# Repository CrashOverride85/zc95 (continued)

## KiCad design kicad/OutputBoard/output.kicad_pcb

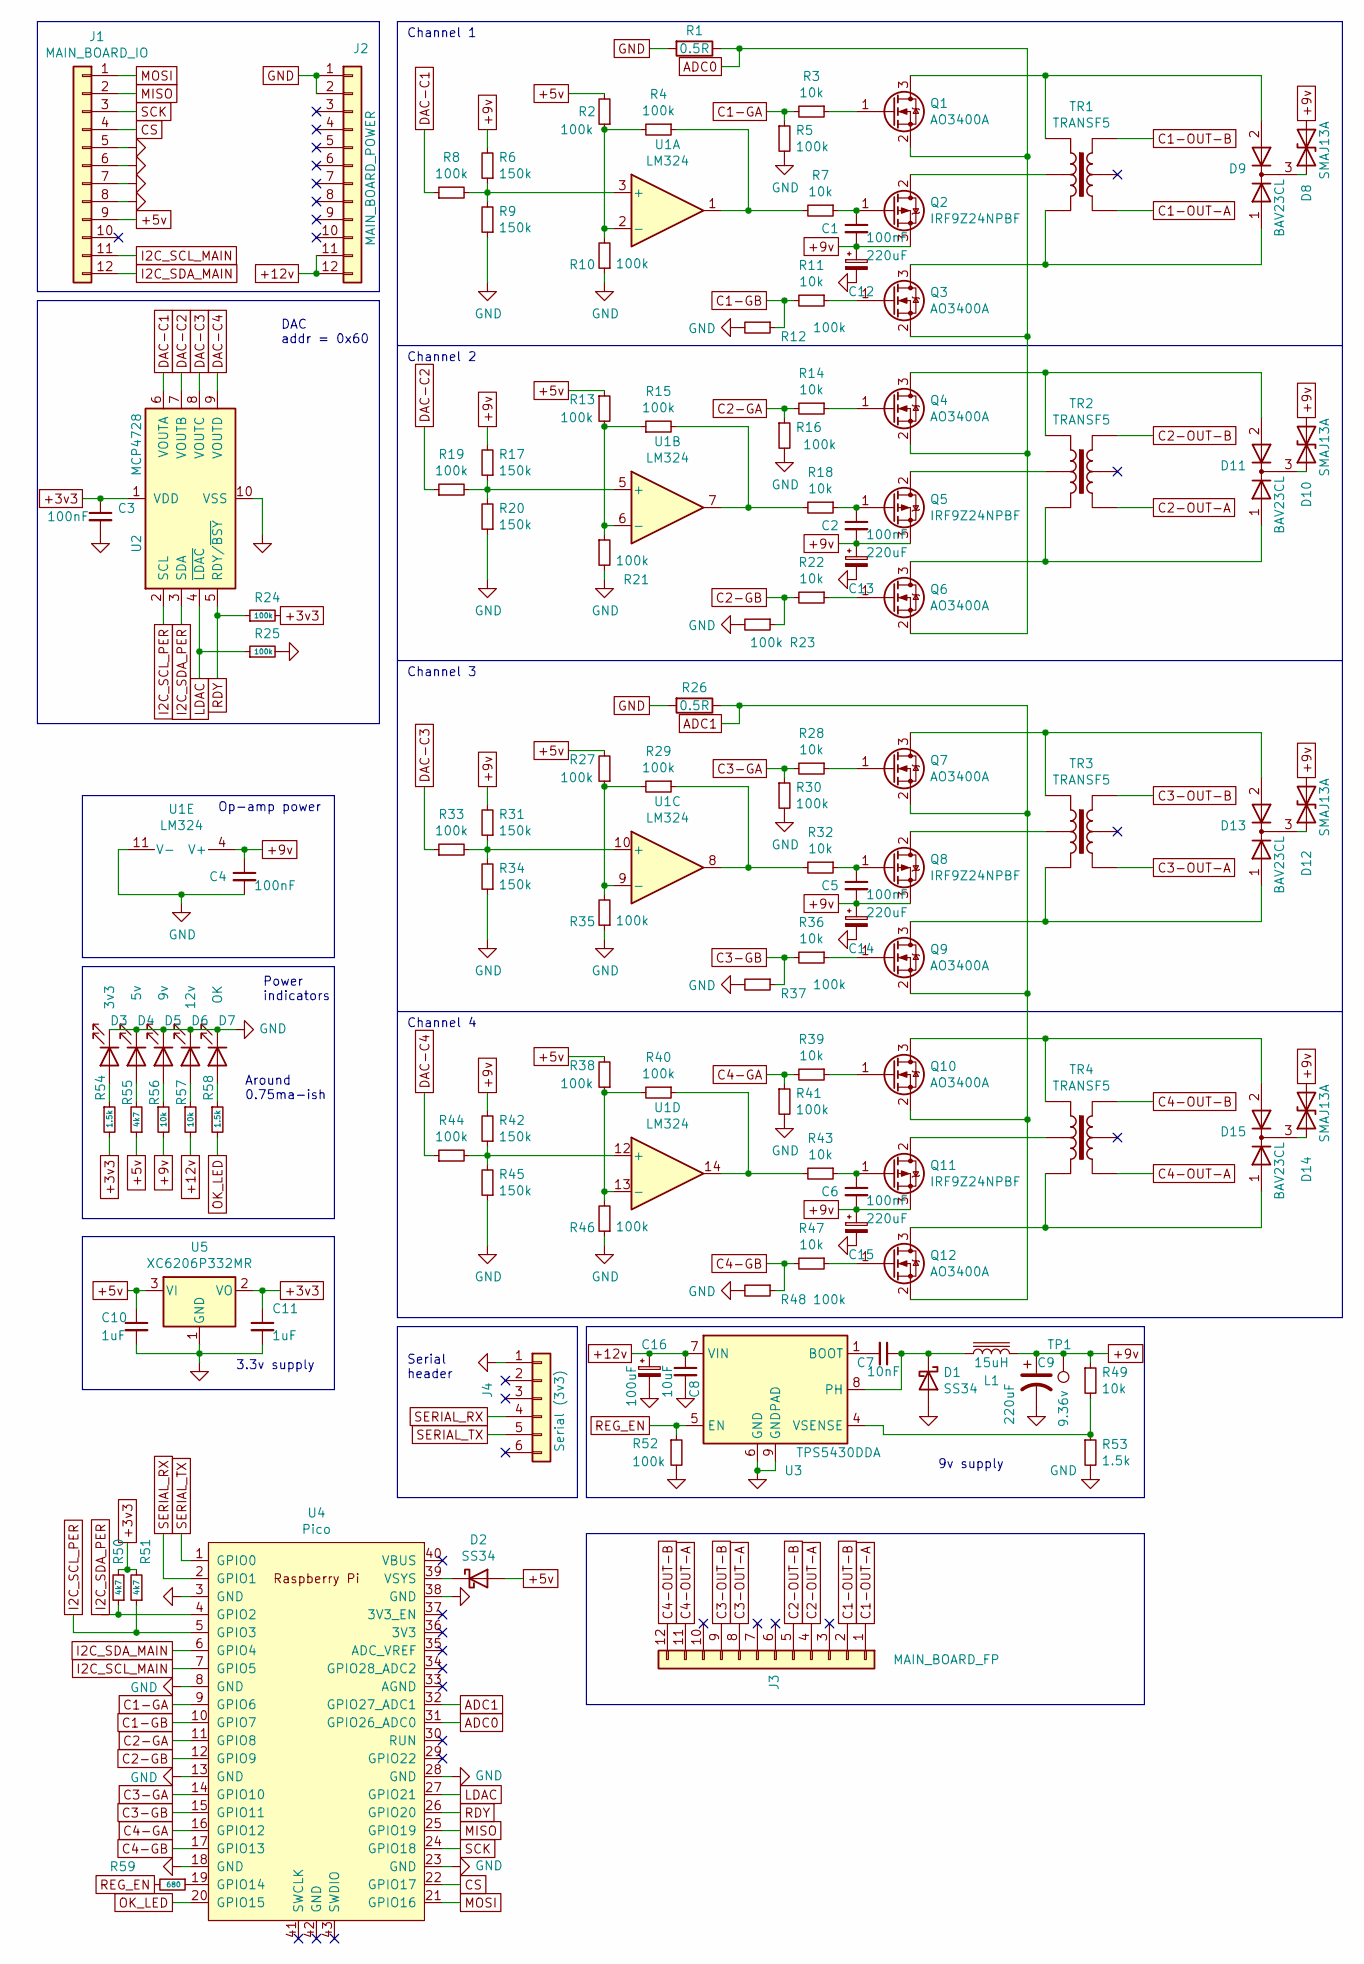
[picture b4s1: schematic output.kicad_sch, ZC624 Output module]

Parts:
C1, C2, C3, C4, C5, C6: 100nF; C_0603_1608Metric_Pad1.08x0.95mm_HandSolder; LCSC C49678
C7: 10nF; C_0603_1608Metric_Pad1.08x0.95mm_HandSolder; LCSC C57112
C8: 10uF; C_0603_1608Metric_Pad1.08x0.95mm_HandSolder; LCSC C15850
C9: 220uF; CP_Radial_D8.0mm_P3.50mm; LCSC C440836
C10, C11: 1uF; C_0603_1608Metric_Pad1.08x0.95mm_HandSolder; LCSC C28323
C12, C13, C14, C15: 220uF; CP_EIA-7343-43_Kemet-X_Pad2.25x2.55mm_HandSolder; LCSC C122311
C16: 100uF; CP_Radial_D5.0mm_P2.00mm; LCSC C108360
D1, D2: SS34; D_SMA; LCSC C8678
D3: 3v3; LED_0603_1608Metric_Pad1.05x0.95mm_HandSolder; LCSC C2986059
D4: 5v; LED_0603_1608Metric_Pad1.05x0.95mm_HandSolder; LCSC C2986059
D5: 9v; LED_0603_1608Metric_Pad1.05x0.95mm_HandSolder; LCSC C2986059
D6: 12v; LED_0603_1608Metric_Pad1.05x0.95mm_HandSolder; LCSC C2986059
D7: OK; LED_0603_1608Metric_Pad1.05x0.95mm_HandSolder; LCSC C2986059
D8, D10, D12, D14: SMAJ13A; D_SMA; LCSC C110519
D9, D11, D13, D15: BAV23CL; SOT-23-3; LCSC C232533
J1: MAIN_BOARD_IO; PinHeader_1x12_P2.54mm_Vertical
J2: MAIN_BOARD_POWER; PinHeader_1x12_P2.54mm_Vertical
J3: MAIN_BOARD_FP; PinHeader_1x12_P2.54mm_Vertical
J4: Serial (3v3); PinHeader_1x06_P2.54mm_Vertical
L1: 15uH; L_7.3x7.3_H3.5; LCSC C177243
Q1, Q3, Q4, Q6, Q7, Q9, Q10, Q12: AO3400A; SOT-23_Handsoldering; LCSC C20917
Q2, Q5, Q8, Q11: IRF9Z24NPBF; TO-220-3_Vertical; LCSC C2576
R1, R26: 0.5R; R_Axial_DIN0309_L9.0mm_D3.2mm_P5.08mm_Vertical; LCSC C479296
R2, R4, R5, R8, R10, R12, R13, R15, R16, R19, R21, R23, R24, R25, R27, R29, R30, R33, R35, R37, R38, R40, R41, R44, R46, R48, R52: 100k; R_0603_1608Metric_Pad0.98x0.95mm_HandSolder; LCSC C149504
R3, R7, R11, R14, R18, R22, R28, R32, R36, R39, R43, R47, R49, R56, R57: 10k; R_0603_1608Metric_Pad0.98x0.95mm_HandSolder; LCSC C17414
R6, R9, R17, R20, R31, R34, R42, R45: 150k; R_0603_1608Metric_Pad0.98x0.95mm_HandSolder; LCSC C17470
R50, R51, R55: 4k7; R_0603_1608Metric_Pad0.98x0.95mm_HandSolder; LCSC C23162
R53, R54, R58: 1.5k; R_0603_1608Metric_Pad0.98x0.95mm_HandSolder; LCSC C4310
R59: 680; R_0603_1608Metric_Pad0.98x0.95mm_HandSolder; LCSC C17798
TP1: 9.36v; TestPoint_Pad_2.5x2.5mm
TR1, TR2, TR3, TR4: TRANSF5; 42TL+U
U1: LM324; SOIC-14_3.9x8.7mm_P1.27mm; LCSC C71035
U2: MCP4728; MSOP-10_3x3mm_P0.5mm; LCSC C108207
U3: TPS5430DDA; TI_SO-PowerPAD-8_ThermalVias; LCSC C9864
U4: Pico; RPi_Pico_SMD_TH
U5: XC6206P332MR; SOT-23; LCSC C5446

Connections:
+3v3: C3.1, C11.1, R24.2, R50.2, R51.2, R54.2, U2.1 (VDD), U5.2 (VO)
+5v: C10.1, D2.2 (A), J1.9, R2.2, R13.1, R27.2, R38.2, R55.1, U5.3 (VI)
+9v: C1.2, C2.2, C4.1, C5.2, C6.2, C9.1, C12.1, C13.1, C14.1, C15.1, D8.2 (A2), D10.2 (A2), D12.2 (A2), D14.2 (A2), L1.2, Q2.3 (S), Q5.3 (S), Q8.3 (S), Q11.3 (S), R6.2, R17.2, R31.2, R42.2, R49.1, R56.2, TP1.1, U1.4 (V+)
+12v: C8.1, C16.1, J2.11, J2.12, R57.2, U3.7 (VIN)
ADC0: Q1.2 (S), Q3.2 (S), Q4.2 (S), Q6.2 (S), R1.1, U4.31 (GPIO26_ADC0)
ADC1: Q7.2 (S), Q9.2 (S), Q10.2 (S), Q12.2 (S), R26.1, U4.32 (GPIO27_ADC1)
C1-GA: R3.2, R5.1, U4.9 (GPIO6)
C1-GB: R11.2, R12.1, U4.10 (GPIO7)
C1-OUT-A: J3.1, TR1.4
C1-OUT-B: J3.2, TR1.6
C2-GA: R14.2, R16.1, U4.11 (GPIO8)
C2-GB: R22.2, R23.1, U4.12 (GPIO9)
C2-OUT-A: J3.4, TR2.4
C2-OUT-B: J3.5, TR2.6
C3-GA: R28.2, R30.1, U4.14 (GPIO10)
C3-GB: R36.2, R37.1, U4.15 (GPIO11)
C3-OUT-A: J3.8, TR3.4
C3-OUT-B: J3.9, TR3.6
C4-GA: R39.2, R41.1, U4.16 (GPIO12)
C4-GB: R47.2, R48.1, U4.17 (GPIO13)
C4-OUT-A: J3.11, TR4.4
C4-OUT-B: J3.12, TR4.6
CS: J1.4, U4.22 (GPIO17)
DAC-C1: R8.1, U2.6 (VOUTA)
DAC-C2: R19.1, U2.7 (VOUTB)
DAC-C3: R33.1, U2.8 (VOUTC)
DAC-C4: R44.1, U2.9 (VOUTD)
GND: C3.2, C4.2, C8.2, C9.2, C10.2, C11.2, C12.2, C13.2, C14.2, C15.2, C16.2, D1.2 (A), D3.1 (K), D4.1 (K), D5.1 (K), D6.1 (K), D7.1 (K), J1.5, J1.6, J1.7, J1.8, J2.1, J2.2, J4.1, R1.2, R5.2, R9.1, R10.1, R12.2, R16.2, R20.1, R21.2, R23.2, R25.2, R26.2, R30.2, R34.1, R35.1, R37.2, R41.2, R45.1, R46.1, R48.2, R52.2, R53.2, U1.11 (V-), U2.10 (VSS), U3.6 (GND), U3.9 (GNDPAD), U4.3 (GND), U4.8 (GND), U4.13 (GND), U4.18 (GND), U4.23 (GND), U4.28 (GND), U4.38 (GND), U5.1 (GND)
I2C_SCL_MAIN: J1.11, U4.7 (GPIO5)
I2C_SCL_PER: R51.1, U2.2 (SCL), U4.5 (GPIO3)
I2C_SDA_MAIN: J1.12, U4.6 (GPIO4)
I2C_SDA_PER: R50.1, U2.3 (SDA), U4.4 (GPIO2)
LDAC: R25.1, U2.4 (~LDAC), U4.27 (GPIO21)
MISO: J1.2, U4.25 (GPIO19)
MOSI: J1.1, U4.21 (GPIO16)
unnamed: C1.1, Q2.1 (G), R7.1
unnamed: C2.1, Q5.1 (G), R18.1
unnamed: C5.1, Q8.1 (G), R32.1
unnamed: C6.1, Q11.1 (G), R43.1
unnamed: C7.1, D1.1 (K), L1.1, U3.8 (PH)
unnamed: C7.2, U3.1 (BOOT)
unnamed: D2.1 (K), U4.39 (VSYS)
unnamed: D3.2 (A), R54.1
unnamed: D4.2 (A), R55.2
unnamed: D5.2 (A), R56.1
unnamed: D6.2 (A), R57.1
unnamed: D7.2 (A), R58.1
unnamed: D8.1 (A1), D9.3 (K)
unnamed: D9.1 (A), Q3.3 (D), TR1.3
unnamed: D9.2 (A), Q1.3 (D), TR1.1
unnamed: D10.1 (A1), D11.3 (K)
unnamed: D11.1 (A), Q6.3 (D), TR2.3
unnamed: D11.2 (A), Q4.3 (D), TR2.1
unnamed: D12.1 (A1), D13.3 (K)
unnamed: D13.1 (A), Q9.3 (D), TR3.3
unnamed: D13.2 (A), Q7.3 (D), TR3.1
unnamed: D14.1 (A1), D15.3 (K)
unnamed: D15.1 (A), Q12.3 (D), TR4.3
unnamed: D15.2 (A), Q10.3 (D), TR4.1
unnamed: Q1.1 (G), R3.1
unnamed: Q2.2 (D), TR1.2
unnamed: Q3.1 (G), R11.1
unnamed: Q4.1 (G), R14.1
unnamed: Q5.2 (D), TR2.2
unnamed: Q6.1 (G), R22.1
unnamed: Q7.1 (G), R28.1
unnamed: Q8.2 (D), TR3.2
unnamed: Q9.1 (G), R36.1
unnamed: Q10.1 (G), R39.1
unnamed: Q11.2 (D), TR4.2
unnamed: Q12.1 (G), R47.1
unnamed: R4.1, R7.2, U1.1
unnamed: R6.1, R8.2, R9.2, U1.3 (+)
unnamed: R2.1, R4.2, R10.2, U1.2 (-)
unnamed: R13.2, R15.1, R21.1, U1.6 (-)
unnamed: R15.2, R18.2, U1.7
unnamed: R17.1, R19.2, R20.2, U1.5 (+)
unnamed: R27.1, R29.2, R35.2, U1.9 (-)
unnamed: R29.1, R32.2, U1.8
unnamed: R31.1, R33.2, R34.2, U1.10 (+)
unnamed: R38.1, R40.2, R46.2, U1.13 (-)
unnamed: R40.1, R43.2, U1.14
unnamed: R42.1, R44.2, R45.2, U1.12 (+)
unnamed: R49.2, R53.1, U3.4 (VSENSE)
unnamed: R59.1, U4.19 (GPIO14)
OK_LED: R58.2, U4.20 (GPIO15)
RDY: R24.1, U2.5 (RDY/~BSY), U4.26 (GPIO20)
REG_EN: R52.1, R59.2, U3.5 (EN)
SCK: J1.3, U4.24 (GPIO18)
SERIAL_RX: J4.4, U4.2 (GPIO1)
SERIAL_TX: J4.5, U4.1 (GPIO0)

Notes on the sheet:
Serial header
Channel 1
Channel 2
DAC addr = 0x60
Power indicators
9v supply
Channel 4
Op-amp power
Channel 3
3.3v supply
Around 0.75ma-ish

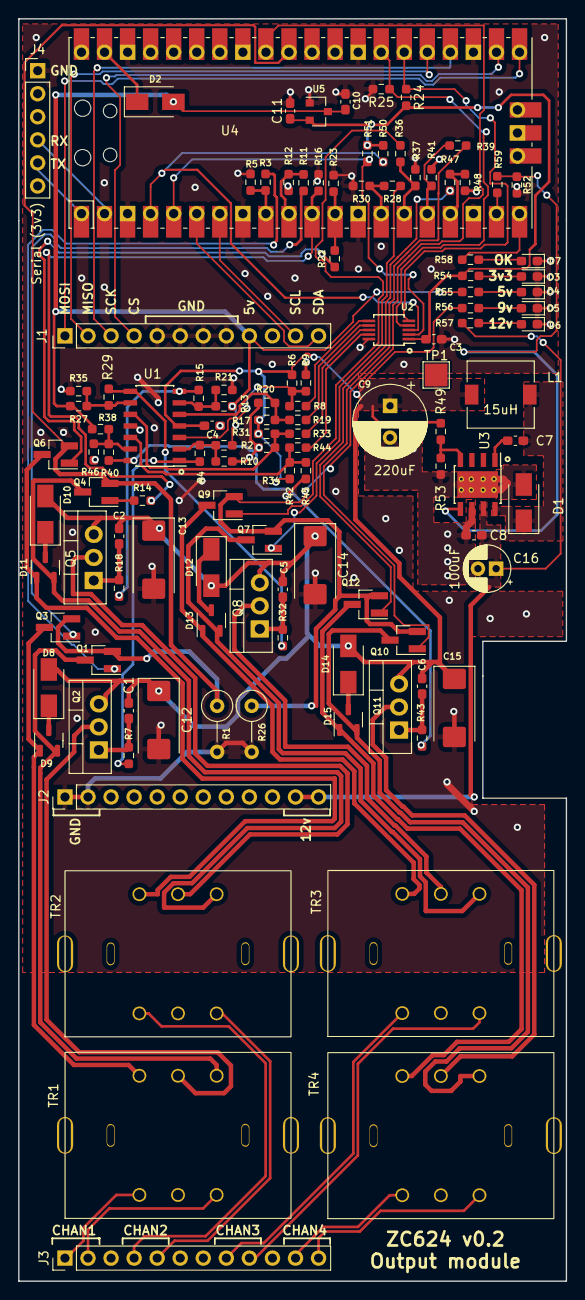
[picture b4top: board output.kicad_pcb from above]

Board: 2 copper layers, 60.3 x 139.1 mm, 117 parts (0 on the bottom side), 91 nets.

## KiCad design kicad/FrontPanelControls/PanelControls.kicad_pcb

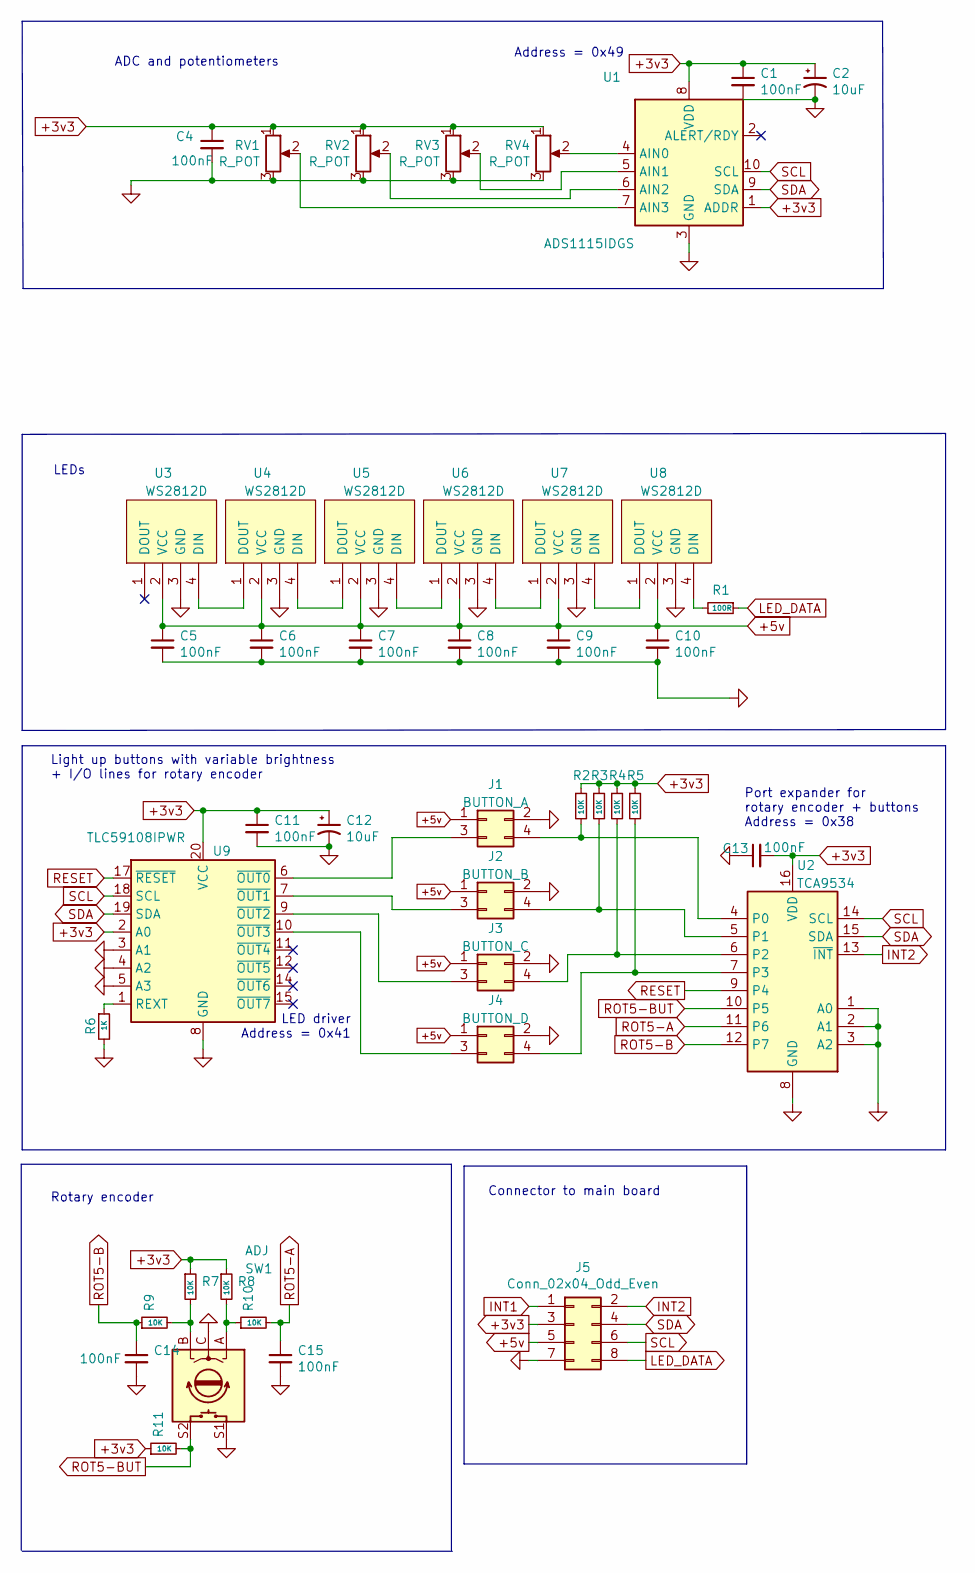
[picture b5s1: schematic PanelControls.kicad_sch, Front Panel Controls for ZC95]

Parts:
C1, C4, C5, C6, C7, C8, C9, C10, C11, C13, C14, C15: 100nF; C_0603_1608Metric_Pad1.08x0.95mm_HandSolder; LCSC C14663
C2, C12: 10uF; C_0603_1608Metric_Pad1.08x0.95mm_HandSolder; LCSC C19702
J1: BUTTON_A; ButtonConnector
J2: BUTTON_B; ButtonConnector
J3: BUTTON_C; ButtonConnector
J4: BUTTON_D; ButtonConnector
J5: Conn_02x04_Odd_Even; IDC-Header_2x04_P2.54mm_Vertical
R1: 100R; R_0603_1608Metric_Pad0.98x0.95mm_HandSolder; LCSC C22775
R2, R3, R4, R5, R7, R8, R9, R10, R11: 10K; R_0603_1608Metric_Pad0.98x0.95mm_HandSolder; LCSC C25804
R6: 1K; R_0603_1608Metric_Pad0.98x0.95mm_HandSolder; LCSC C21190
RV1, RV2, RV3, RV4: R_POT; ALPSALPINE RK09L1140A2U
SW1: ADJ; BOURNS PEC11L-4125F-S0020
U1: ADS1115IDGS; TSSOP-10_3x3mm_P0.5mm
U2: TCA9534; TSSOP-16_4.4x5mm_P0.65mm; LCSC C206010
U3, U4, U5, U6, U7, U8: WS2812D; WS2812D-F5
U9: TLC59108IPWR; TSSOP-20_4.4x6.5mm_P0.65mm; LCSC C130031

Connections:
+3v3: C1.1, C2.1, C4.1, C11.1, C12.1, C13.2, J5.3, R2.1, R3.1, R4.1, R5.1, R7.1, R8.1, R11.1, RV1.1, RV2.1, RV3.1, RV4.1, U1.1 (ADDR), U1.8 (VDD), U2.16 (VDD), U9.2 (A0), U9.20 (VCC)
+5v: C5.1, C6.1, C7.1, C8.1, C9.1, C10.1, J1.1, J2.1, J3.1, J4.1, J5.5, U3.2 (VCC), U4.2 (VCC), U5.2 (VCC), U6.2 (VCC), U7.2 (VCC), U8.2 (VCC)
GND: C1.2, C2.2, C4.2, C5.2, C6.2, C7.2, C8.2, C9.2, C10.2, C11.2, C12.2, C13.1, C14.2, C15.2, J1.2, J2.2, J3.2, J4.2, J5.7, R6.2, RV1.3, RV2.3, RV3.3, RV4.3, SW1.C, SW1.S1, U1.3 (GND), U2.1 (A0), U2.2 (A1), U2.3 (A2), U2.8 (GND), U3.3 (GND), U4.3 (GND), U5.3 (GND), U6.3 (GND), U7.3 (GND), U8.3 (GND), U9.3 (A1), U9.4 (A2), U9.5 (A3), U9.8 (GND), U9.13 (GND), U9.16 (GND)
INT1: J5.1
INT2: J5.2, U2.13 (~INT)
LED_DATA: J5.8, R1.1
unnamed: J1.3, U9.6 (~OUT0)
unnamed: J1.4, R2.2, U2.4 (P0)
unnamed: J2.3, U9.7 (~OUT1)
unnamed: J2.4, R3.2, U2.5 (P1)
unnamed: J3.3, U9.9 (~OUT2)
unnamed: J3.4, R4.2, U2.6 (P2)
unnamed: J4.3, U9.10 (~OUT3)
unnamed: J4.4, R5.2, U2.7 (P3)
unnamed: R1.2, U8.4 (DIN)
unnamed: R6.1, U9.1 (REXT)
unnamed: R7.2, R9.2, SW1.B
unnamed: R8.2, R10.1, SW1.A
unnamed: RV1.2, U1.7 (AIN3)
unnamed: RV2.2, U1.6 (AIN2)
unnamed: RV3.2, U1.5 (AIN1)
unnamed: RV4.2, U1.4 (AIN0)
unnamed: U3.4 (DIN), U4.1 (DOUT)
unnamed: U4.4 (DIN), U5.1 (DOUT)
unnamed: U5.4 (DIN), U6.1 (DOUT)
unnamed: U6.4 (DIN), U7.1 (DOUT)
unnamed: U7.4 (DIN), U8.1 (DOUT)
RESET: U2.9 (P4), U9.17 (~RESET)
ROT5-A: C15.1, R10.2, U2.11 (P6)
ROT5-B: C14.1, R9.1, U2.12 (P7)
ROT5-BUT: R11.2, SW1.S2, U2.10 (P5)
SCL: J5.6, U1.10 (SCL), U2.14 (SCL), U9.18 (SCL)
SDA: J5.4, U1.9 (SDA), U2.15 (SDA), U9.19 (SDA)

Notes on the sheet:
Rotary encoder
Light up buttons with variable brightness + I/O lines for rotary encoder
Port expander for rotary encoder + buttons Address = 0x38
Connector to main board
ADC and potentiometers
LEDs
Address = 0x49
LED driver Address = 0x41

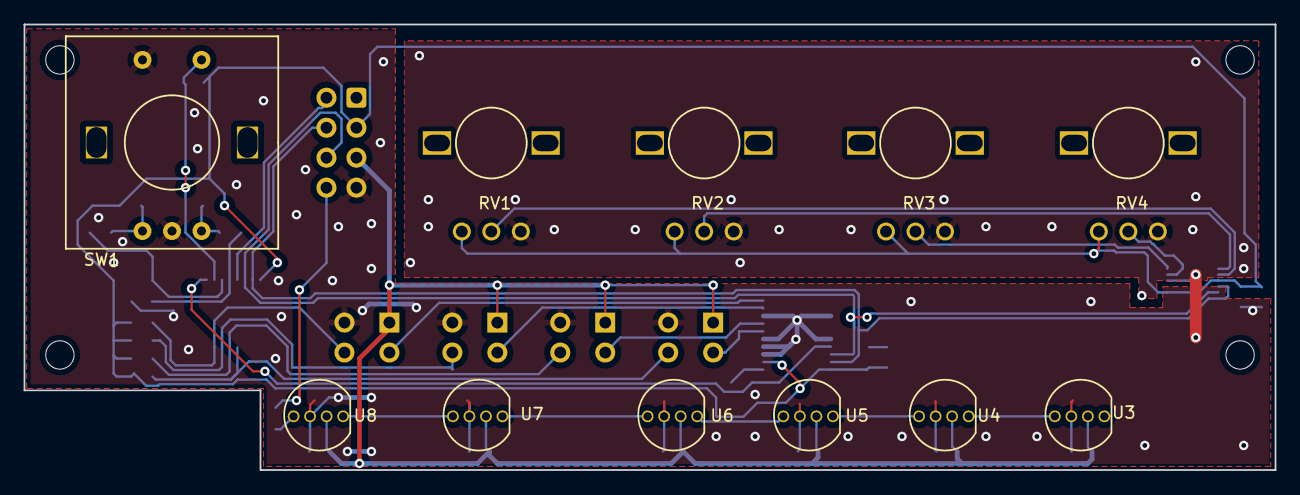
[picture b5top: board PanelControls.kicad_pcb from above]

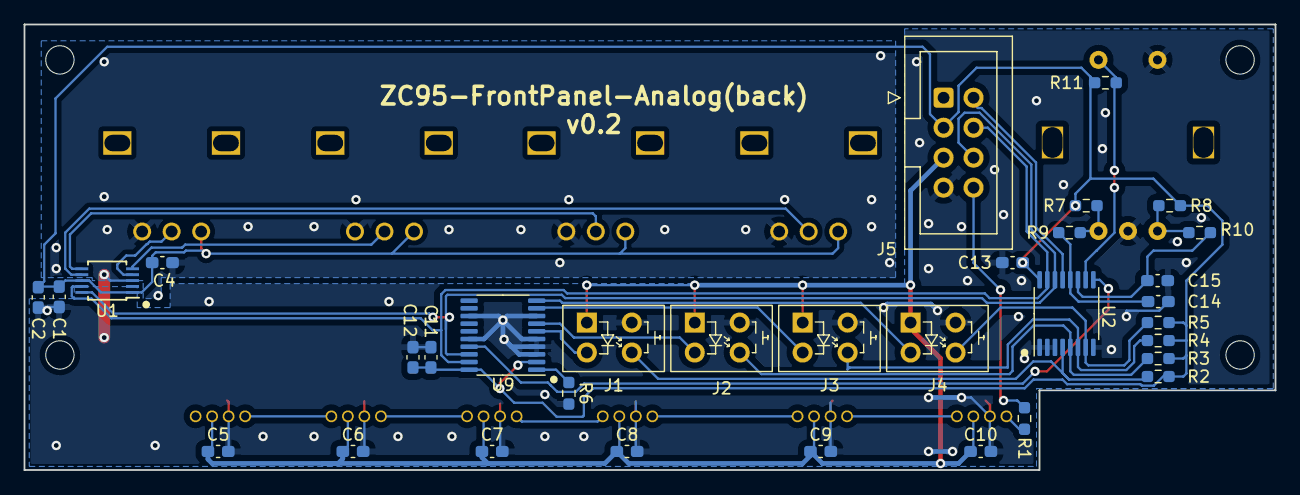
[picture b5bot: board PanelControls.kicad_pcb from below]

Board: 2 copper layers, 106.0 x 37.8 mm, 44 parts (33 on the bottom side), 32 nets.

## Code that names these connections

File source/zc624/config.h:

#ifndef _CCONFIG_H
#define _CCONFIG_H

// SPI Defines
// We are going to use SPI 0, and allocate it to the following GPIO pins
/*

    SPIx_SCK = SCK
    SPIx_TX = MOSI
    SPIx_RX = MISO
*/

#define SPI_PORT spi0
#define PIN_SPI_MOSI 16 // RX
#define PIN_SPI_CS   17
#define PIN_SPI_SCK  18
#define PIN_SPI_MISO 19 // TX
#define SPI_BAUD_RATE 500000


// I2C defines

// For connection to on board DAC (so we are i2c master)
#define I2C_PORT_PER i2c1
#define I2C_SDA_PER 2
#define I2C_SCL_PER 3

#define DAC_ADDRESS 0x60

// For connection to main board (so we are i2c slave)
#define I2C_PORT_SLAVE i2c0
#define I2C_SDA_SLAVE 4
#define I2C_SCL_SLAVE 5
#define ZC624_ADDR  0x10 // our address


#define DEVICE_TYPE   624
#define VERSION_MAJOR   2
#define VERSION_MINOR   1




#define PIN_9V_ENABLE   14
#define PIN_OK_LED      15

#define PIN_CHAN1_GATE_A 6
#define PIN_CHAN1_GATE_B 7

#define PIN_CHAN2_GATE_A 8
#define PIN_CHAN2_GATE_B 9

#define PIN_CHAN3_GATE_A 10
#define PIN_CHAN3_GATE_B 11

#define PIN_CHAN4_GATE_A 12
#define PIN_CHAN4_GATE_B 13

#endif

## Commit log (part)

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2023-08-17 fix issue where wrong pattern could be started if audio hardware not present
2023-08-17 fix issue where wrong pattern could be started if audio hardware not present (#55)
2023-08-18 Add a backplate OpenSCAD file and STL for a 3d printed backplate with (#57)
2023-08-19 show power level in bar graph
2023-08-20 show power level in 3x scaled font on change
2023-08-20 update documentation to match
2023-08-20 Show power level percent (#58)
    Adds the option to show a numeric/percentage power level display, Allows display of power level:
    * In large-ish text for a few moments on change. Based on code linked to in #52
    * In small text, all the time, in the bar graph
    Can be configured from settings -> Display options -> power level display.
2023-08-22 allow loop frequency to be set for Lua scripts
2023-08-23 More explicit setting of wifi power mode
    Use cyw43_pm_value to set the wifi power mode. The call results in the
    exact same value as before (0xa11140), but makes it more explicit what
    is happening. It also makes it easier to adjust the power management in
    the future.
2023-08-23 show error if invalid loop freq set in Lua script
2023-08-23 urldecode wifi access point ssid and password (#61)
    * More explicit setting of wifi power mode
    Use cyw43_pm_value to set the wifi power mode. The call results in the
    exact same value as before (0xa11140), but makes it more explicit what
    is happening. It also makes it easier to adjust the power management in
    the future.
    * urldecode wifi ssid and password
2023-08-23 Don't display Up/Down button text if there is no action - fixes #59
2023-08-26 Update build notes and BoM
2023-08-28 set LED state using data from zc624, addresses #62.
    Makes LEDs when running a Lua script respond in a similar way to in built patterns like waves, climb, etc.
2023-08-29 Update LED display so Lua scripts don't just show solid red (#65)
    Makes LEDs when running a Lua script respond in a similar way to in built patterns like waves, climb, etc.
    Need to update both zc95 & zc624 firmwares.
2023-09-03 Embed 2x Lua scripts: Waves and Orgasm
2023-09-16 spi tweaks
2023-09-16 documentation changes to match pattern changes
2023-09-16 Embed lua scripts (#66)
    Embed Lua scripts for Waves, Climb and Orgasm
2023-10-07 tweak comms between zc95 & zc624 to reduce jitter in output
2023-10-07 use OK LED on zc624. Improve error display on zc95 when output board init fails
2023-10-07 Use OK LED on zc624 & improve error reporting (#69)
    * use OK LED on zc624. Improve error display on zc95 when output board init fails
    * add note to build docs / troubleshooting section about the OK LED
2023-10-08 test SPI comms between main board and output board on startup (#70)
2023-10-14 fix issue where pin 6 (front panel interupt) was being driven high. Fixes #71
2023-10-20 add comments to new/inbult lua scripts about origin
2023-10-20 add note to lua docs about inbult lua patterns
2023-10-21 on panic, try and make sure both cores halt and the output board is shutdown
2023-10-29 fix debug output from arduino lib
2023-11-17 first version of Zc95 Arduino lib - wifi/websocket
2023-11-20 tweak tracking of connection status
2023-11-22 add zc95 arduino serial example
2023-12-11 updated gerbers & schematic
2023-12-11 Update BoM and PCB readme
2023-12-31 v0.2 of front panel. light up led buttons, new adc, new i/o expander
2024-01-01 tidy up FrontPanelControls directory
2024-01-01 update gerbers, add cpl/bom files for front panel controls board, update pcb changelog
2024-01-01 start updating build notes, update front panel pcbs after generating gerbers
2024-01-01 update schematic pdf, and tweak formatting of schematic
2024-01-01 update gitignore to include gerbers in kicad folder & jlcpcb prep stuff
2024-01-27 New front panel working, but not using LEDs yet
2024-01-27 Set button LEDs depending on if button is active
2024-02-05 tweak readme
2024-02-08 update docs
2024-02-11 tidy
2024-02-11 New front panel (#86)
    v0.2 of front panel. light up led buttons, new adc, new i/o expander
2024-02-23 with verbose bt hid output logging
2024-02-24 show connection status and button being pressed on bluetooth test page. Fix up reconnection logic
2024-02-25 add battery icon and remove 'BAT: xx% text'
2024-02-27 tweaks and comments
2024-02-29 make Lua script slot 0 48k instead of 24k like the rest, add a progress bar when uploading, and increase the timeout in the python scripts so they don't time out when waiting for a large lua script t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
2024-02-29 48k lua slot 0 + add upload progress bar (#87)
    (cherry picked from commit 705441ac055ed6cf2a9fe6df95553e1e33738baf)
2024-03-02 Fix issue with new front panel where power level graphs didn't get updated when first entering remote mode, and a button press was registered at startup that wasn't there
2024-03-02 Save mappings between keypress and action
2024-03-04 Allow bluetooth remotes to be used with routines, and allow key press to be passed through to Lua scripts
2024-03-08 tweak bluetooth menus
2024-03-15 tweaks, tidying and documentation
2024-03-16 allow button brightness to be reduced further than before
2024-03-16 build notes tweaks
2024-03-20 fix icons.h
2024-03-20 fix crash on starting some patterns remotely (#90)
    Fix crash on starting some patterns remotely
2024-03-27 make bt hid queue global, and init at startup
2024-03-27 allow bluetooth to connect in serial remote access mode
2024-04-21 when uploading a lua script, don't allocate the full 24k/48k in memory and write to flash at the end, instead write to flash in 4k blocks during upload
2024-04-21 fix issue where large script would casue a crash on upload (#92)
    * fix issue where large script would casue a crash on upload
    * when uploading a lua script, don't allocate the full 24k/48k in memory and write to flash at the end, instead write to flash in 4k blocks during upload
2024-05-04 Receive events from custom Bluetooth HID devices (#93)
2024-05-19 BT WIP
2024-06-04 BLE WIP - fw mostly done
2024-06-08 can enable/diable channel, set power level, and allow changing between limiting and scaling power based on front panel setting
2024-06-09 add intense and toggle python patterns
2024-06-12 pulse streaming from python pretty much working
2024-06-13 more documentation changes
2024-06-13 update build notes - btstack needs python to generate something in the gatt file
2024-06-15 pattern list not updating after lua upload
2024-06-15 add intense pattern
2024-06-15 allow settings power level to high/medium/low
2024-06-15 move ramp time into new output menu
2024-06-15 Power level setting - High / Medium / Low (#98)
2024-06-17 allow audio intensity from Lua to work (to some degree) over wifi
2024-06-17 add lua audio example and update lua notes
2024-06-18 include patterns using audio intensity when running remotly
2024-06-18 Allow Lua scripts to react to audio volume (#99)
2024-06-23 tweak permitted calibration values
2024-06-25 update BoM to strikethrough J16 on main board
2024-06-25 Add notes on LED riser
2024-07-06 tweak hw check so that state of LED driver IC on front panel doesn't affect detection of front panel version
2024-08-01 fix issue where shock collars are using potentially stale configuration
2024-08-01 increase pulse length for 4th channel on shock choice pattern + tweak collar logic
2024-08-16 Update AudioInput-Build.md
    D3 silkscreen wrong, thanks electro991 for identifying it
2024-08-17 Increase shockchoice pulse length (#113)
    * increase pulse length for 4th channel on shock choice pattern + tweak collar logic
    * tweak so that a longer pulse is sent to chan4 in shoch choice pattern
2024-08-17 allow rotary encoder to be used on pattern selection list and a couple of others (#116)
2024-09-01 fix 0805/0603 mixup (#120)
2024-09-01 correct link text for front panel bom and cpl files
2024-09-10 update R1 and R26 of output board to be C479327 instead of C479296 (#121)
2024-10-26 Add rhythm pattern
2024-10-26 fix drc errors
2024-10-26 add new production files
2024-10-27 add random2
2024-10-30 tweaks to climb.lua and ettot.lua
2024-11-01 Right align the right hand button labels, then they are closer to the buttons. Assume the font size, everything else does and nothing seems to define the width. Move the button label texts down one p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
2024-11-02 Alignment of button labels in GUI (#128)
    Right align the right hand button labels, then they are closer to the buttons. Assume the font size, everything else does and nothing seems to define the width.
    Move the button label texts down one pixel so they look better centered.
2024-11-02 Fix build with 2.0 SDK (#129)
2024-11-02 Allow rotary encoder button use; enable more menus
    Enables rotary encoder use in more menus. Allow the rotary encoder button function to be used as "select".
2024-11-03 tweak for v0.1 front panel - waves was starting on power up
2024-11-03 Allow rotary encoder button use; enable more menus (#130)
2024-11-03 only populate the pattern list when first displaying it, don't regenerate it from scratch when returning
2024-11-03 New patterns: phasing2, stroke, rhythm, torment, combo, random2 (#127)
2024-11-05 update BoM & build notes
2024-11-05 add update schematic pdf
2024-11-06 Audio input board redesign for SMT (#133)
2024-12-03 fix build issue that appeared after update to sdk 2.1.0
2024-12-03 fix bug where pattern list wasn't refreshed after new pattern uploaded
2025-03-26 fix board outline for front panel and mainboad (#139)
2025-03-28 Ble menu issue (#141)
    * fix #140 where BLE peripherals screen could crash
2025-04-18 update PDF schematics
2025-04-18 documentation update
2025-04-18 some renaming
2025-04-18 update firmware
2025-04-27 fix solder mask minimum width setting, then regenerate gerbers
2025-04-29 Documentation tweaks
2025-05-25 update out of stock 0.5R resistor C705591 to be C175573 instead
2025-06-12 fix typo BQ72441 -> BQ27441
2025-06-20 improve error messages when hardware check fails
2025-06-20 as of SDK 2.1.1 the RP2040 is certified for 200MHz - take advantage of that
2025-07-31 new schematic pdf
2025-07-31 tweak power management
2025-08-02 basic triphase
2025-08-02 improved triphase
2025-08-22 Notes on 100uF cap between switch and ground
2025-09-15 Mainboard PCB v2.4
2025-10-17 update production files, schematic pdf, and change log
2025-10-18 remove note at top of build notes about v2.3
2025-10-26 Update serial control instructions for ZC95 MKII
    Clarified serial control instructions for ZC95, specifying aux/serial port details and jumper settings for MKII.
2025-11-06 update ic2 address for TCA9534 -> TCA9534A
2025-11-07 also update address of mk1 equiv. so hardware version detection works
2025-11-28 Change C50 on main board from 4.7nF to 47nF
2025-12-14 include serial number in VersionDetails message
2025-12-15 allow Lua scripts to update menu options
2025-12-21 update multi choice options on change in python ui
2025-12-21 fix display not updating when multi-choice option changed from script
2025-12-21 Add Lua SetMenuOption (#155)
    Allow Lua scripts to change their own parameters
2025-12-22 tweak error messages
2026-01-03 beginings of new tens pattern
2026-01-03 add pulse rate modulation mode
2026-01-05 Tidy up pattern
2026-01-05 fix typo and update patterns.md
2026-01-17 fix issue where buttons were unresponse on mk1 with front panel 0.1
2026-01-17 Fix issue where buttons were unresponse on mk1 with front panel 0.1 (#160, #159)
2026-01-24 add config for extended ramp
2026-02-02 do ramp up
2026-02-02 allow ramp option to be hidden
2026-02-02 update documentation
2026-02-06 C58 on the mainboard should be 10uF not 10nF
2026-02-16 updated production files
2026-02-19 remove pin header from internal line in socket
2026-02-19 Try i2c bus recovery after adc read errors
2026-03-03 Update BoM: remove C58 (now marked DNP) and swap for C72
2026-03-07 Pcb v2.6 (#167)
2026-03-22 allow front panel LED colour format to be changed
2026-04-10 Add bootloaders for zc95 & zc624, along with a python utility to update the firmware using a USB<>Serial cable connected to the 3.5mm serial socket
2026-04-10 add inital dockerfile and instructions to use it
2026-04-10 Add dockerfile to build firmware (#171)
2026-04-12 build zc95 for pico2
2026-04-16 update dockerfile and notes to build for pico2
2026-05-04 update audio wave pattern to allow impact of audio volume on output to be altered
2026-05-08 allow ramp shape to be set, changed and saved. Not used yet
2026-05-08 apply ramp shape when pattern & ramp running
2026-05-23 allow display of ramp progress on status bar
2026-05-24 allow input on the 3 ACC I/O lines
2026-05-31 update web server to use the SDK supplied pico_set_lwip_httpd_content to build the fsdata file
2026-05-31 add basic web page to allow upload of Lua scripts when connected to WiFi
2026-06-07 fix Lua math.randomseed()
2026-06-14 allow lua scripts to use serial over accessory port
2026-06-18 Allow Lua scripts to use the serial I/O on the accessory port (#178)
